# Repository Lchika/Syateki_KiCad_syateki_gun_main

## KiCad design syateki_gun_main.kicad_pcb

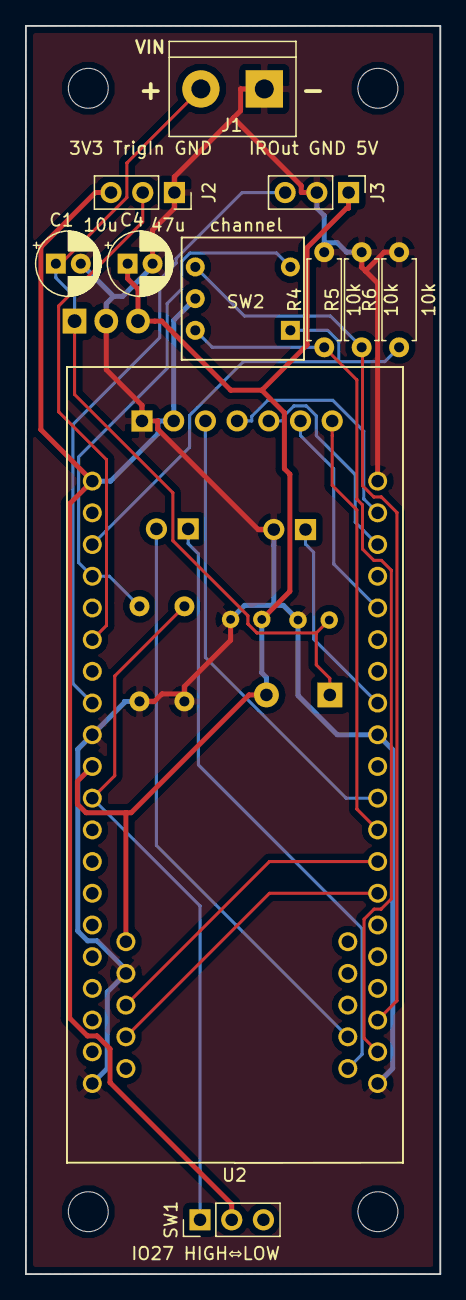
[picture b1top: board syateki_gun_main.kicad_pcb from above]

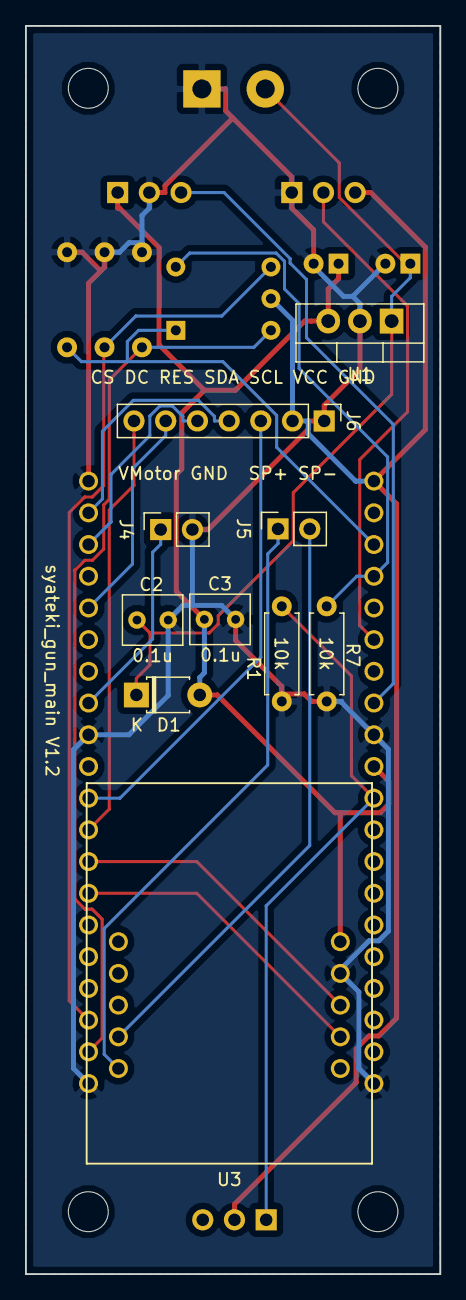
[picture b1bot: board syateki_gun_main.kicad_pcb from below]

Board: 2 copper layers, 33.2 x 100.0 mm, 25 parts (10 on the bottom side), 21 nets.

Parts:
C1: 10u; CP_Radial_D5.0mm_P2.00mm
C2, C3: 0.1u; C_Rect_L4.6mm_W3.8mm_P2.50mm_MKS02_FKP02
C4: 47u; CP_Radial_D5.0mm_P2.00mm
D1: D; D_T-1_P5.08mm_Horizontal
J1: Screw_Terminal_01x02; TerminalBlock_bornier-2_P5.08mm
J2: Conn_01x03_Female; PinSocket_1x03_P2.54mm_Vertical
J3: Conn_01x03_Female; PinHeader_1x03_P2.54mm_Vertical
J4, J5: Conn_01x02_Female; PinSocket_1x02_P2.54mm_Vertical
J6: Conn_01x07_Female; PinHeader_1x07_P2.54mm_Vertical
R1, R4, R5, R6, R7: 10k; R_Axial_DIN0207_L6.3mm_D2.5mm_P7.62mm_Horizontal
SW1: SW_SPDT; PinHeader_1x03_P2.54mm_Vertical
SW2: SW_Coded_SH-7040; rotary_sw10
U1: L7805; TO-220-3_Vertical
U2: ESPr-Developer-32; ESP-Developer32
U3: MP3_Voice_Module
hole1, hole2, hole3, hole4: MountingHole_3.2mm_M3

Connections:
3.3V: J2.3, J6.2, SW1.2, SW2.C, U2.1
5V: C3.1, C4.1, D1.2, J3.1, U1.3, U2.10, U3.5
GND: C1.2, C2.2, C3.2, C4.2, J1.1, J2.1, J3.2, J4.2, J6.1, R1.2, R4.2, R5.2, R6.2, R7.2, U1.2, U2.9, U2.20, U2.21, U2.32, U2.40, U3.4
IO34: R4.1, SW2.4, U2.22
IO35: R5.1, SW2.8, U2.23
unnamed: C1.1, C2.1, D1.1, J1.2, U1.1
unnamed: J2.2, U2.6
unnamed: J3.3, U2.8
unnamed: J4.1, U2.33
unnamed: J5.1, U3.10
unnamed: J5.2, U3.9
unnamed: J6.3, U2.30
unnamed: J6.4, U2.39
unnamed: J6.5, U2.38
unnamed: J6.6, U2.36
unnamed: J6.7, U2.29
unnamed: R1.1, SW1.1, U2.11
unnamed: R6.1, SW2.1, U2.3
unnamed: R7.1, SW2.2, U2.4
unnamed: U2.27, U3.2
unnamed: U2.28, U3.3
